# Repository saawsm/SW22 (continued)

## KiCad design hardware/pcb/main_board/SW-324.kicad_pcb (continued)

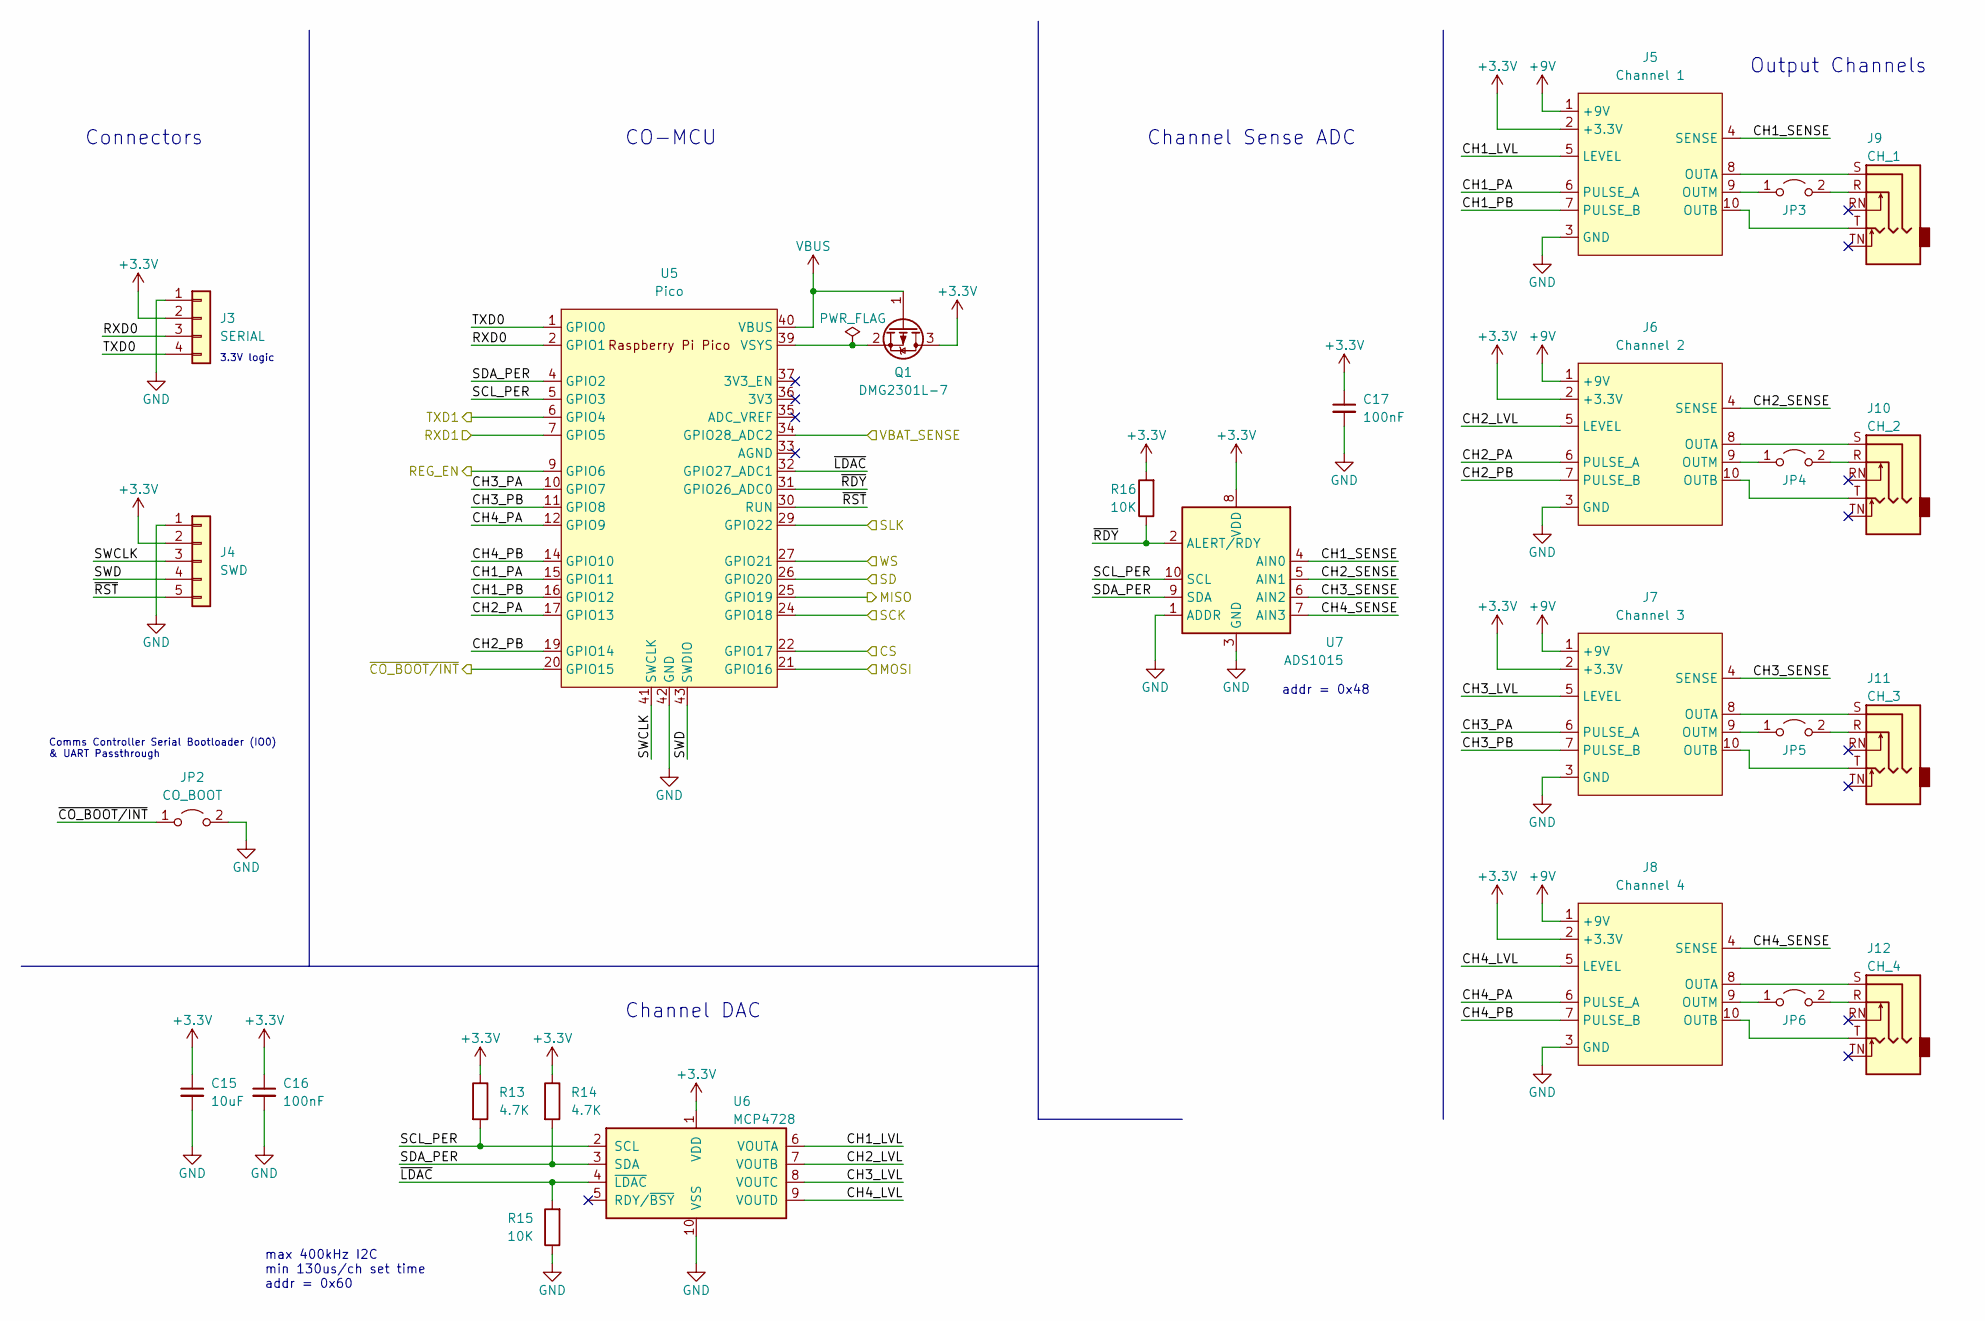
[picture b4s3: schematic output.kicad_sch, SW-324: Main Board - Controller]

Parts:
C15: 10uF; C_0603_1608Metric; MPN CL10A106MA8NRNC; MOUSER 187-CL10A106MA8NRNC
C16, C17: 100nF; C_0603_1608Metric; MPN CL10B104KB8NNNC; MOUSER 187-CL10B104KB8NNNC
J3: SERIAL; PinHeader_1x04_P2.54mm_Vertical
J4: SWD; PinHeader_1x05_P2.54mm_Vertical
J5: Channel 1; SW-32MO_Socket
J6: Channel 2; SW-32MO_Socket
J7: Channel 3; SW-32MO_Socket
J8: Channel 4; SW-32MO_Socket
J9: CH_1; STX-3100-5N; MPN STX-3100-5N; MOUSER 806-STX-3100-5N
J10: CH_2; STX-3100-5N; MPN STX-3100-5N; MOUSER 806-STX-3100-5N
J11: CH_3; STX-3100-5N; MPN STX-3100-5N; MOUSER 806-STX-3100-5N
J12: CH_4; STX-3100-5N; MPN STX-3100-5N; MOUSER 806-STX-3100-5N
JP2: CO_BOOT; PinHeader_1x02_P2.54mm_Vertical
JP3: JP1; PinHeader_1x02_P2.54mm_Vertical
JP4: JP2; PinHeader_1x02_P2.54mm_Vertical
JP5: JP3; PinHeader_1x02_P2.54mm_Vertical
JP6: JP4; PinHeader_1x02_P2.54mm_Vertical
Q1: DMG2301L-7; SOT-23; MPN DMG2301L-7; LCSC C102619
R13, R14: 4.7K; R_0603_1608Metric; MPN RC0603FR-074K7L; MOUSER 603-RC0603FR-074K7L
R15: 10K; R_0603_1608Metric; MPN RC0603FR-0710KL; LCSC C98220
R16: 10K; R_0603_1608Metric; MPN RC0603FR-0710KL; MOUSER 603-RC0603FR-0710KL
U5: Pico; RPi_Pico_SMD; MPN RASPBERRY PI PICO (UNSOLDERED); MOUSER 713-102110537
U6: MCP4728; MSOP-10_3x3mm_P0.5mm; MPN MCP4728-E/UN; LCSC C108207
U7: ADS1015; TSSOP-10_3x3mm_P0.5mm; MPN ADS1015IDGSR; LCSC C193969

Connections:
+3V3: C15.1, C16.1, C17.1, J3.2, J4.2, J5.2 (+3.3V), J6.2 (+3.3V), J7.2 (+3.3V), J8.2 (+3.3V), Q1.3 (D), R13.1, R14.1, R16.2, U6.1 (VDD), U7.8 (VDD); also elsewhere on the board
+9V: J5.1 (+9V), J6.1 (+9V), J7.1 (+9V), J8.1 (+9V); also elsewhere on the board
/Comms Controller/MISO: U5.25 (GPIO19); also elsewhere on the board
/Comms Controller/MOSI: U5.21 (GPIO16); also elsewhere on the board
/Comms Controller/RXD: U5.6 (GPIO4); also elsewhere on the board
/Comms Controller/SCK: U5.29 (GPIO22); also elsewhere on the board
/Comms Controller/SD: U5.26 (GPIO20); also elsewhere on the board
/Comms Controller/SLK: U5.24 (GPIO18); also elsewhere on the board
/Comms Controller/TXD: U5.7 (GPIO5); also elsewhere on the board
/Comms Controller/WS: U5.27 (GPIO21); also elsewhere on the board
/Comms Controller/~BOOT/INT: JP2.1 (A), U5.20 (GPIO15); also elsewhere on the board
/Comms Controller/~CS: U5.22 (GPIO17); also elsewhere on the board
/Controller/CH1_LVL: J5.5 (LEVEL), U6.6 (VOUTA)
/Controller/CH1_PA: J5.6 (PULSE_A), U5.15 (GPIO11)
/Controller/CH1_PB: J5.7 (PULSE_B), U5.16 (GPIO12)
/Controller/CH1_SENSE: J5.4 (SENSE), U7.4 (AIN0)
/Controller/CH2_LVL: J6.5 (LEVEL), U6.7 (VOUTB)
/Controller/CH2_PA: J6.6 (PULSE_A), U5.17 (GPIO13)
/Controller/CH2_PB: J6.7 (PULSE_B), U5.19 (GPIO14)
/Controller/CH2_SENSE: J6.4 (SENSE), U7.5 (AIN1)
/Controller/CH3_LVL: J7.5 (LEVEL), U6.8 (VOUTC)
/Controller/CH3_PA: J7.6 (PULSE_A), U5.10 (GPIO7)
/Controller/CH3_PB: J7.7 (PULSE_B), U5.11 (GPIO8)
/Controller/CH3_SENSE: J7.4 (SENSE), U7.6 (AIN2)
/Controller/CH4_LVL: J8.5 (LEVEL), U6.9 (VOUTD)
/Controller/CH4_PA: J8.6 (PULSE_A), U5.12 (GPIO9)
/Controller/CH4_PB: J8.7 (PULSE_B), U5.14 (GPIO10)
/Controller/CH4_SENSE: J8.4 (SENSE), U7.7 (AIN3)
/Controller/REG_EN: U5.9 (GPIO6); also elsewhere on the board
/Controller/RXD0: J3.3, U5.2 (GPIO1)
/Controller/SCL_PER: R13.2, U5.5 (GPIO3), U6.2 (SCL), U7.10 (SCL)
/Controller/SDA_PER: R14.2, U5.4 (GPIO2), U6.3 (SDA), U7.9 (SDA)
/Controller/SWCLK: J4.3, U5.41 (SWCLK)
/Controller/SWD: J4.4, U5.43 (SWDIO)
/Controller/TXD0: J3.4, U5.1 (GPIO0)
/Controller/VBAT_SENSE: U5.34 (GPIO28_ADC2); also elsewhere on the board
/Controller/~LDAC: R15.2, U5.32 (GPIO27_ADC1), U6.4 (~LDAC)
/Controller/~RDY: R16.1, U5.31 (GPIO26_ADC0), U7.2 (ALERT/RDY)
/Controller/~RST: J4.5, U5.30 (RUN)
GND: C15.2, C16.2, C17.2, J3.1, J4.1, J5.3 (GND), J6.3 (GND), J7.3 (GND), J8.3 (GND), JP2.2 (B), R15.1, U5.3 (GND), U5.8 (GND), U5.13 (GND), U5.18 (GND), U5.23 (GND), U5.28 (GND), U5.38 (GND), U5.42 (GND), U6.10 (VSS), U7.1 (ADDR), U7.3 (GND); also elsewhere on the board
unnamed: J5.8 (OUTA), J9.S
unnamed: J5.9 (OUTM), JP3.1 (A)
unnamed: J5.10 (OUTB), J9.T
unnamed: J6.9 (OUTM), JP4.1 (A)
unnamed: J7.9 (OUTM), JP5.1 (A)
unnamed: J8.9 (OUTM), JP6.1 (A)
unnamed: J9.R, JP3.2 (B)
unnamed: J10.R, JP4.2 (B)
unnamed: J6.8 (OUTA), J10.S
unnamed: J6.10 (OUTB), J10.T
unnamed: J11.R, JP5.2 (B)
unnamed: J7.8 (OUTA), J11.S
unnamed: J7.10 (OUTB), J11.T
unnamed: J12.R, JP6.2 (B)
unnamed: J8.8 (OUTA), J12.S
unnamed: J8.10 (OUTB), J12.T
unnamed: Q1.2 (S), U5.39 (VSYS)
VBUS: Q1.1 (G), U5.40 (VBUS); also elsewhere on the board

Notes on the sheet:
CO-MCU
3.3V logic
addr = 0x48
Comms Controller Serial Bootloader (IO0) & UART Passthrough
Channel Sense ADC
Output Channels
Channel DAC
max 400kHz I2C min 130us/ch set time addr = 0x60
Connectors

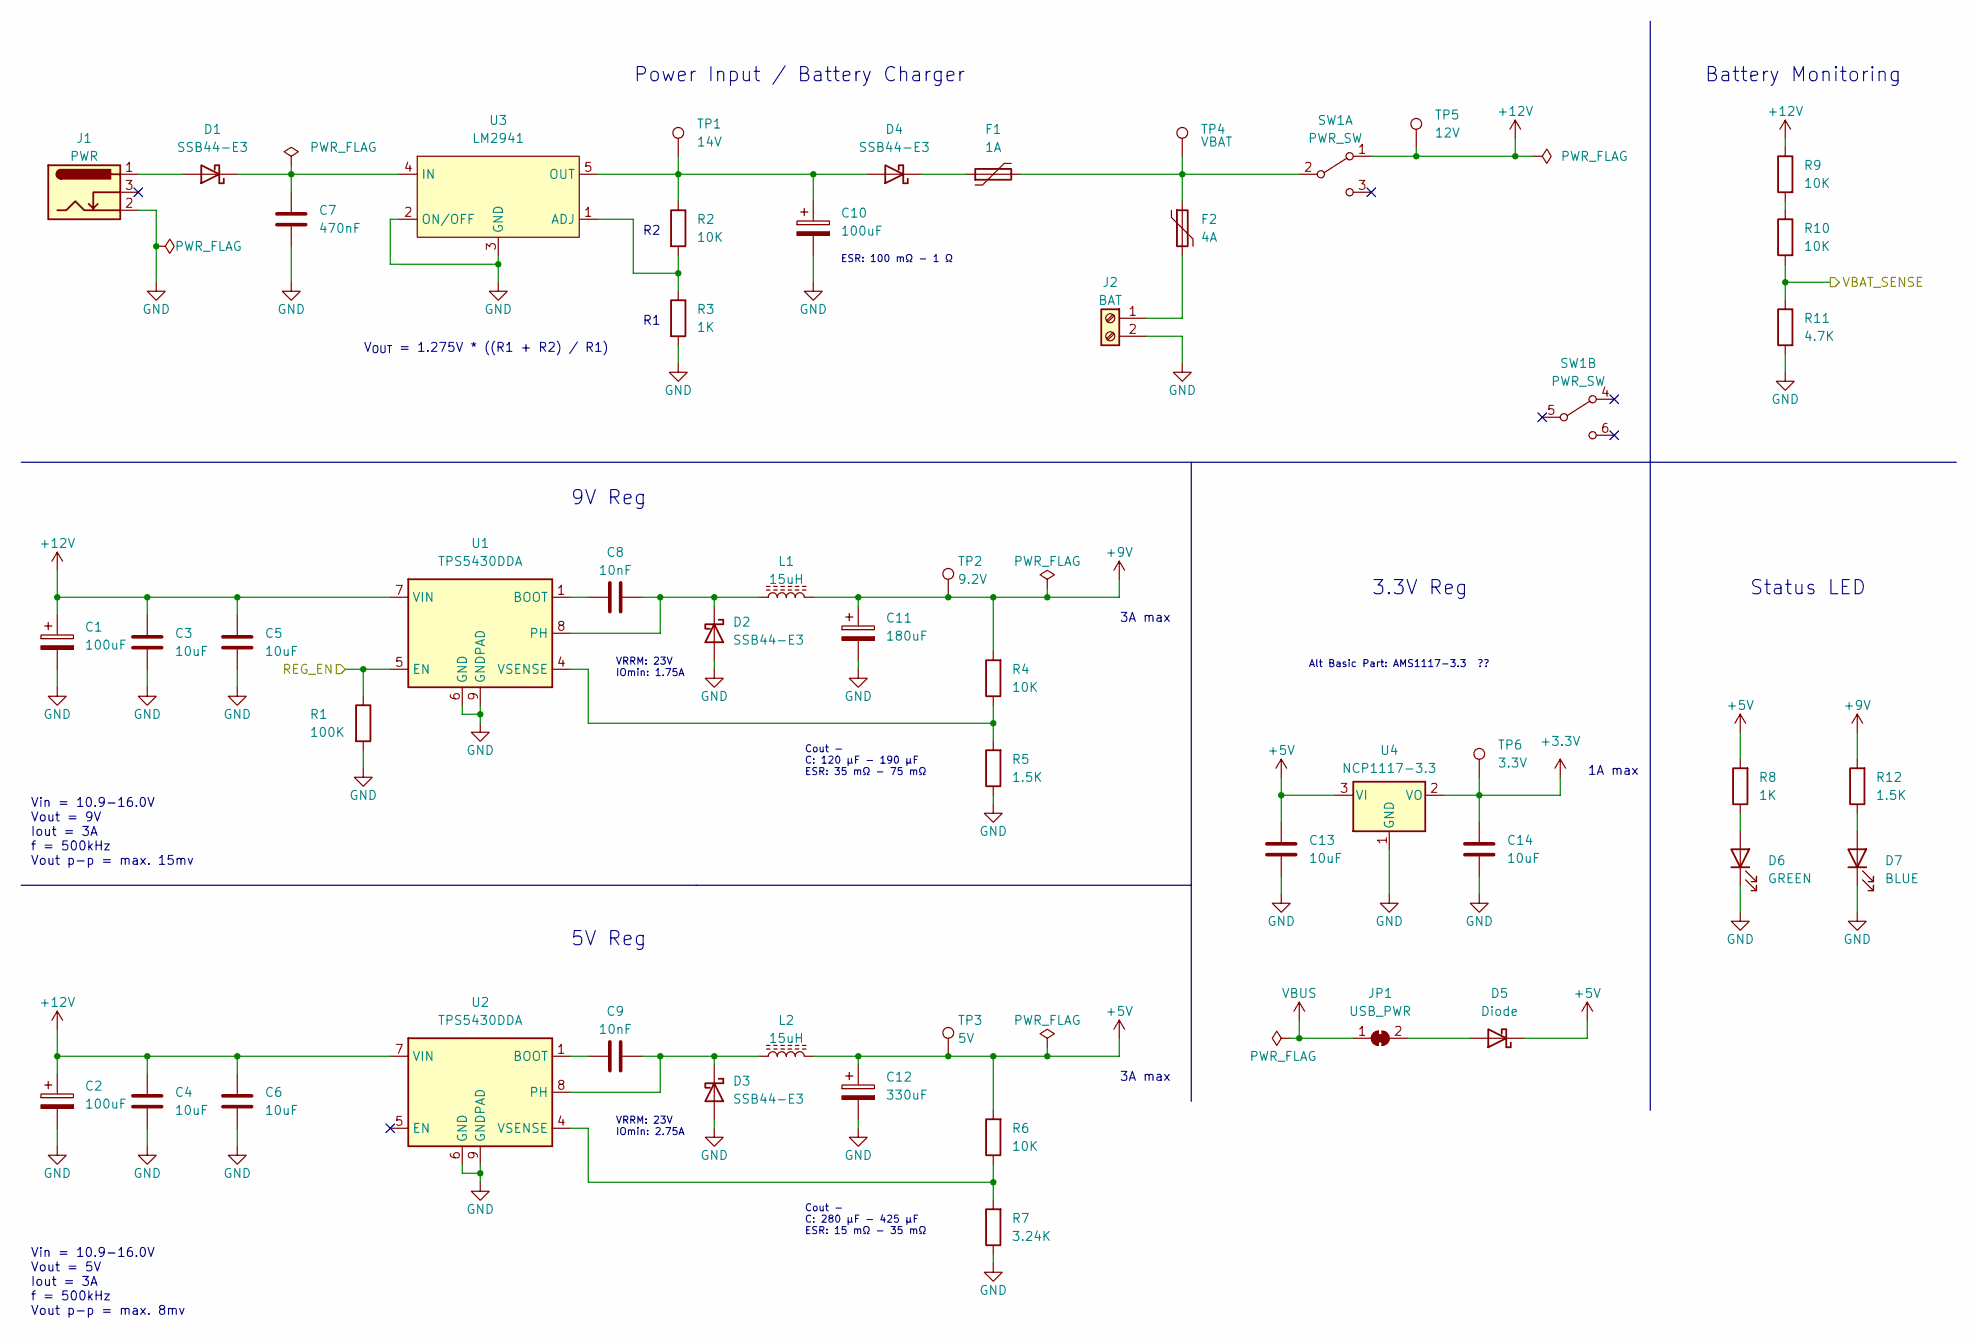
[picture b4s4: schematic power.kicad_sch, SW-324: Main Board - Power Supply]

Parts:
C1, C2, C10: 100uF; CP_Radial_D6.3mm_P2.50mm; MPN EEU-FM1E101; LCSC C1579509
C3, C4, C5, C6: 10uF; C_1210_3225Metric; MPN CL32A106KAJNNNE; LCSC C66120
C7: 470nF; C_0603_1608Metric; MPN CL10A474KB8NNNC; LCSC C170149
C8, C9: 10nF; C_0603_1608Metric; MPN CL10B103KB8NNNC; LCSC C1589
C11: 180uF; CP_Elec_10x7.9; MPN 16SVP180MX; LCSC C236288
C12: 330uF; CP_Elec_10x12.6; MPN 16SVP330M; LCSC C128487
C13, C14: 10uF; C_0603_1608Metric; MPN CL10A106MA8NRNC; MOUSER 187-CL10A106MA8NRNC
D1, D2, D3, D4: SSB44-E3; D_SMB; MPN SSB44-E3/52T; MOUSER 625-SSB44-E3
D5: Diode; D_SOD-123F
D6: GREEN; LED_0603_1608Metric; MPN 150060VS75000; MOUSER 710-150060VS75000
D7: BLUE; LED_0603_1608Metric; MPN 150060BS75000; MOUSER 710-150060BS75000
F1: 1A; Fuse_BelFuse_0ZRE0005FF_L8.3mm_W3.8mm; MPN 72R050XPR; LCSC C207122
F2: 4A; Fuse_BelFuse_0ZRE0016FF_L9.9mm_W3.8mm; MPN RF3357-000; LCSC C142903
J1: PWR; BarrelJack_CUI_PJ-102AH_Horizontal; MPN PJ-102AH; MOUSER 490-PJ-102AH
J2: BAT; JST_XH_B2B-XH-A_1x02_P2.50mm_Vertical
JP1: USB_PWR; SolderJumper-2_P1.3mm_Bridged_RoundedPad1.0x1.5mm
L1, L2: 15uH; L_Bourns_SRR1260; MPN SRR1260-150M; MOUSER 652-SRR1260-150M
R1: 100K; R_0603_1608Metric; MPN RC0603FR-07100KL; MOUSER 603-RC0603FR-07100KL
R2, R4, R6, R9, R10: 10K; R_0603_1608Metric; MPN RC0603FR-0710KL; MOUSER 603-RC0603FR-0710KL
R3, R8: 1K; R_0603_1608Metric; MPN RC0603FR-071KL; MOUSER 603-RC0603FR-071KL
R5: 1.5K; R_0603_1608Metric; MPN RC0603FR-071K5L; LCSC C114668
R7: 3.24K; R_0603_1608Metric; MPN RC0603FR-073K24L; LCSC C273779
R11: 4.7K; R_0603_1608Metric; MPN RC0603FR-074K7L; MOUSER 603-RC0603FR-074K7L
R12: 1.5K; R_0603_1608Metric; MPN RC0603FR-071K5L; MOUSER 603-RC0603FR-071K5L
SW1: PWR_SW; SW_E-Switch_EG2219_DPDT_Angled; MPN EG2219; MOUSER 612-EG2219
TP1: 14V; TestPoint_Pad_D1.5mm
TP2: 9.2V; TestPoint_Pad_D1.5mm
TP3: 5V; TestPoint_Pad_D1.5mm
TP4: VBAT; TestPoint_Pad_D1.5mm
TP5: 12V; TestPoint_Pad_D1.5mm
TP6: 3.3V; TestPoint_Pad_D1.5mm
U1, U2: TPS5430DDA; TI_SO-PowerPAD-8_ThermalVias; MPN TPS5430DDAR; LCSC C9864
U3: LM2941; TO-263-5_TabPin3; MPN LM2941SX/NOPB; LCSC C95046
U4: NCP1117-3.3; SOT-223-3_TabPin2; MPN NCP1117LPST33T3G; LCSC C146799

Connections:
+3V3: C14.1, TP6.1, U4.2 (VO); also elsewhere on the board
+5V: C12.1, C13.1, D5.1 (K), L2.2, R6.2, R8.2, TP3.1, U4.3 (VI); also elsewhere on the board
+9V: C11.1, L1.2, R4.2, R12.2, TP2.1; also elsewhere on the board
+12V: C1.1, C2.1, C3.2, C4.2, C5.2, C6.2, R9.1, SW1.1 (A), TP5.1, U1.7 (VIN), U2.7 (VIN); also elsewhere on the board
/Controller/REG_EN: R1.1, U1.5 (EN); also elsewhere on the board
/Controller/VBAT_SENSE: R10.2, R11.1; also elsewhere on the board
GND: C1.2, C2.2, C3.1, C4.1, C5.1, C6.1, C7.2, C10.2, C11.2, C12.2, C13.2, C14.2, D2.2 (A), D3.2 (A), D6.1 (K), D7.1 (K), J1.2, J2.2, R1.2, R3.2, R5.1, R7.1, R11.2, U1.6 (GND), U1.9 (GNDPAD), U2.6 (GND), U2.9 (GNDPAD), U3.2 (ON/OFF), U3.3 (GND), U4.1 (GND); also elsewhere on the board
unnamed: C7.1, D1.1 (K), U3.4 (IN)
unnamed: C8.1, U1.1 (BOOT)
unnamed: C8.2, D2.1 (K), L1.1, U1.8 (PH)
unnamed: C9.1, U2.1 (BOOT)
unnamed: C9.2, D3.1 (K), L2.1, U2.8 (PH)
unnamed: C10.1, D4.2 (A), R2.1, TP1.1, U3.5 (OUT)
unnamed: D1.2 (A), J1.1
unnamed: D4.1 (K), F1.1
unnamed: D5.2 (A), JP1.2 (B)
unnamed: D6.2 (A), R8.1
unnamed: D7.2 (A), R12.1
unnamed: F1.2, F2.1, SW1.2 (B), TP4.1
unnamed: F2.2, J2.1
unnamed: R2.2, R3.1, U3.1 (ADJ)
unnamed: R4.1, R5.2, U1.4 (VSENSE)
unnamed: R6.1, R7.2, U2.4 (VSENSE)
unnamed: R9.2, R10.1
VBUS: JP1.1 (A); also elsewhere on the board

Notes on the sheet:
Alt Basic Part: AMS1117-3.3 ??
1A max
Cout - C: 120 μF - 190 μF ESR: 35 mΩ - 75 mΩ
VRRM: 23V IOmin: 1.75A
Cout - C: 280 μF - 425 μF ESR: 15 mΩ - 35 mΩ
VRRM: 23V IOmin: 2.75A
5V Reg
9V Reg
3.3V Reg
V_{OUT} = 1.275V * ((R1 + R2) / R1)
Power Input / Battery Charger
ESR: 100 mΩ - 1 Ω
3A max
Battery Monitoring
Vin = 10.9-16.0V Vout = 5V Iout = 3A f = 500kHz Vout p-p = max. 8mv
Vin = 10.9-16.0V Vout = 9V Iout = 3A f = 500kHz Vout p-p = max. 15mv
Status LED

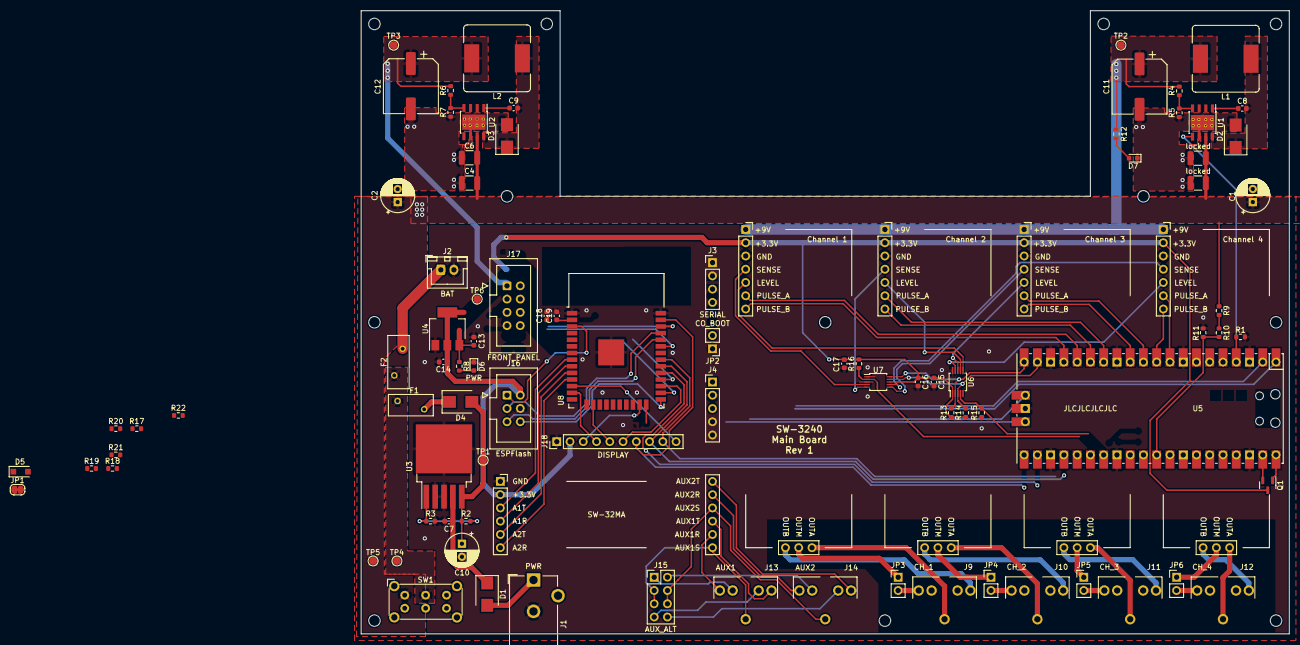
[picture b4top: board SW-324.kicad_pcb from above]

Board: 2 copper layers, 177.8 x 119.4 mm, 105 parts (0 on the bottom side), 102 nets.

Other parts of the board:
locked: 10uF; C_1210_3225Metric
locked#2: 10uF; C_1210_3225Metric

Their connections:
+12V: locked.2, locked#2.2; also elsewhere on the board
GND: locked.1, locked#2.1; also elsewhere on the board

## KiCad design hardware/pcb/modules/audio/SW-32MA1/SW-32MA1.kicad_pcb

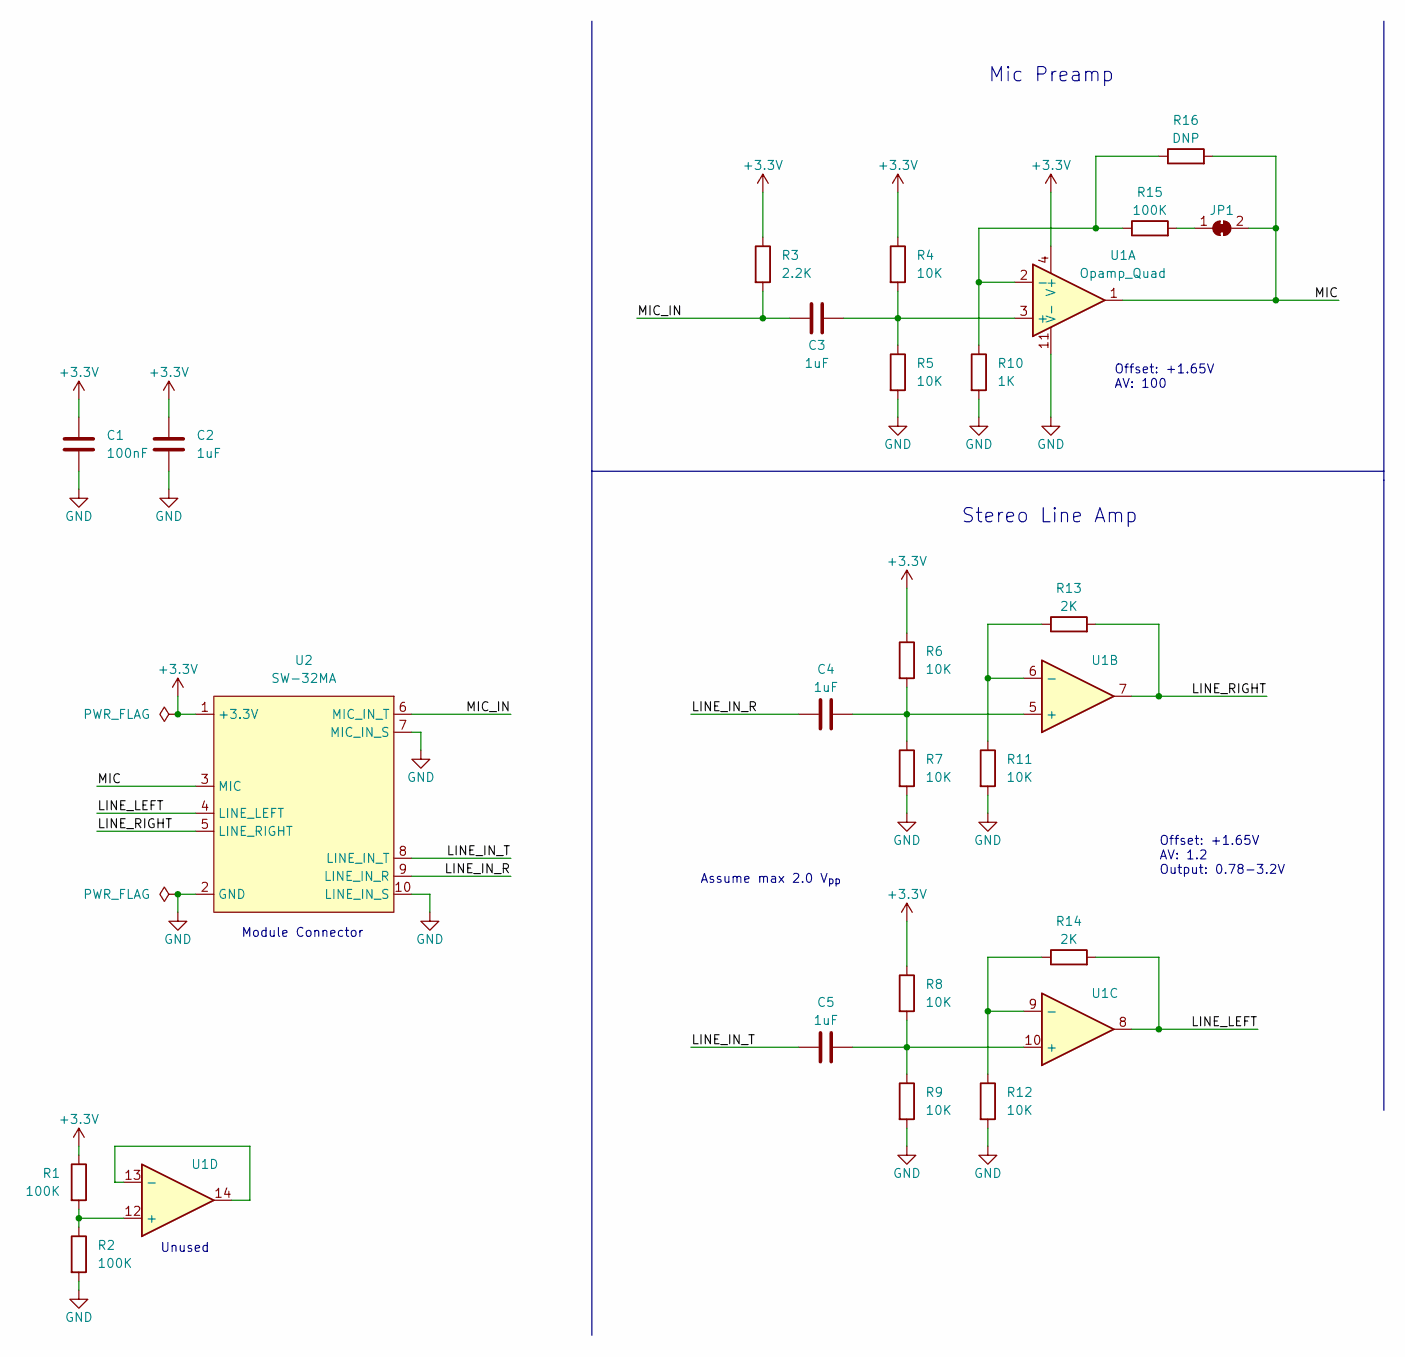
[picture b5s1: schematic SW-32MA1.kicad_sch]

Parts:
C1: 100nF; C_0603_1608Metric
C2, C3, C4, C5: 1uF; C_0603_1608Metric
JP1: SolderJumper_2_Bridged; SolderJumper-2_P1.3mm_Bridged_RoundedPad1.0x1.5mm
R1, R2, R15: 100K; R_0603_1608Metric
R3: 2.2K; R_0603_1608Metric
R4, R5, R6, R7, R8, R9, R11, R12: 10K; R_0603_1608Metric
R10: 1K; R_0603_1608Metric
R13, R14: 2K; R_0603_1608Metric
R16: DNP; R_Axial_DIN0204_L3.6mm_D1.6mm_P5.08mm_Horizontal
U1: Opamp_Quad; SOIC-14_3.9x8.7mm_P1.27mm
U2: SW-32MA; SW-32MA_Header

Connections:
+3V3: C1.2, C2.2, R1.1, R3.1, R4.1, R6.1, R8.1, U1.4 (V+), U2.1 (+3.3V)
/LINE_IN_R: C4.1, U2.9 (LINE_IN_R)
/LINE_IN_T: C5.1, U2.8 (LINE_IN_T)
/LINE_LEFT: R14.2, U1.8, U2.4 (LINE_LEFT)
/LINE_RIGHT: R13.2, U1.7, U2.5 (LINE_RIGHT)
/MIC: JP1.2 (B), R16.2, U1.1, U2.3 (MIC)
/MIC_IN: C3.1, R3.2, U2.6 (MIC_IN_T)
GND: C1.1, C2.1, R2.2, R5.2, R7.2, R9.2, R10.2, R11.2, R12.2, U1.11 (V-), U2.2 (GND), U2.7 (MIC_IN_S), U2.10 (LINE_IN_S)
unnamed: C3.2, R4.2, R5.1, U1.3 (+)
unnamed: C4.2, R6.2, R7.1, U1.5 (+)
unnamed: C5.2, R8.2, R9.1, U1.10 (+)
unnamed: JP1.1 (A), R15.2
unnamed: R1.2, R2.1, U1.12 (+)
unnamed: R10.1, R15.1, R16.1, U1.2 (-)
unnamed: R11.1, R13.1, U1.6 (-)
unnamed: R12.1, R14.1, U1.9 (-)
unnamed: U1.13 (-), U1.14

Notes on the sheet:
Stereo Line Amp
Assume max 2.0 V_{pp}
Mic Preamp
Module Connector
Offset: +1.65V AV: 1.2 Output: 0.78-3.2V
Offset: +1.65V AV: 100
Unused

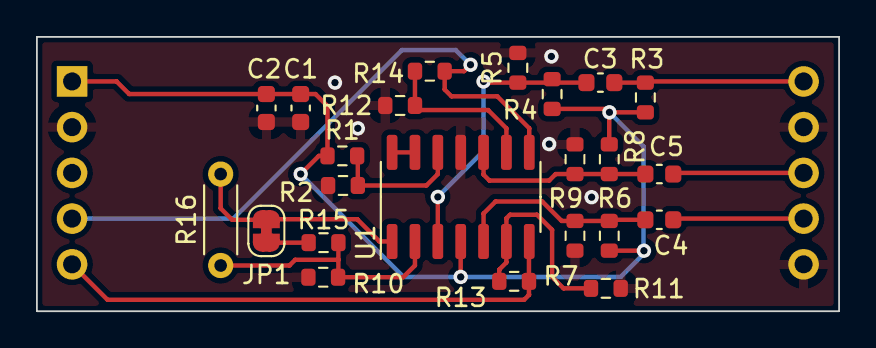
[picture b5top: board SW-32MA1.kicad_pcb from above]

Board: 2 copper layers, 44.6 x 15.2 mm, 24 parts (0 on the bottom side), 17 nets.
